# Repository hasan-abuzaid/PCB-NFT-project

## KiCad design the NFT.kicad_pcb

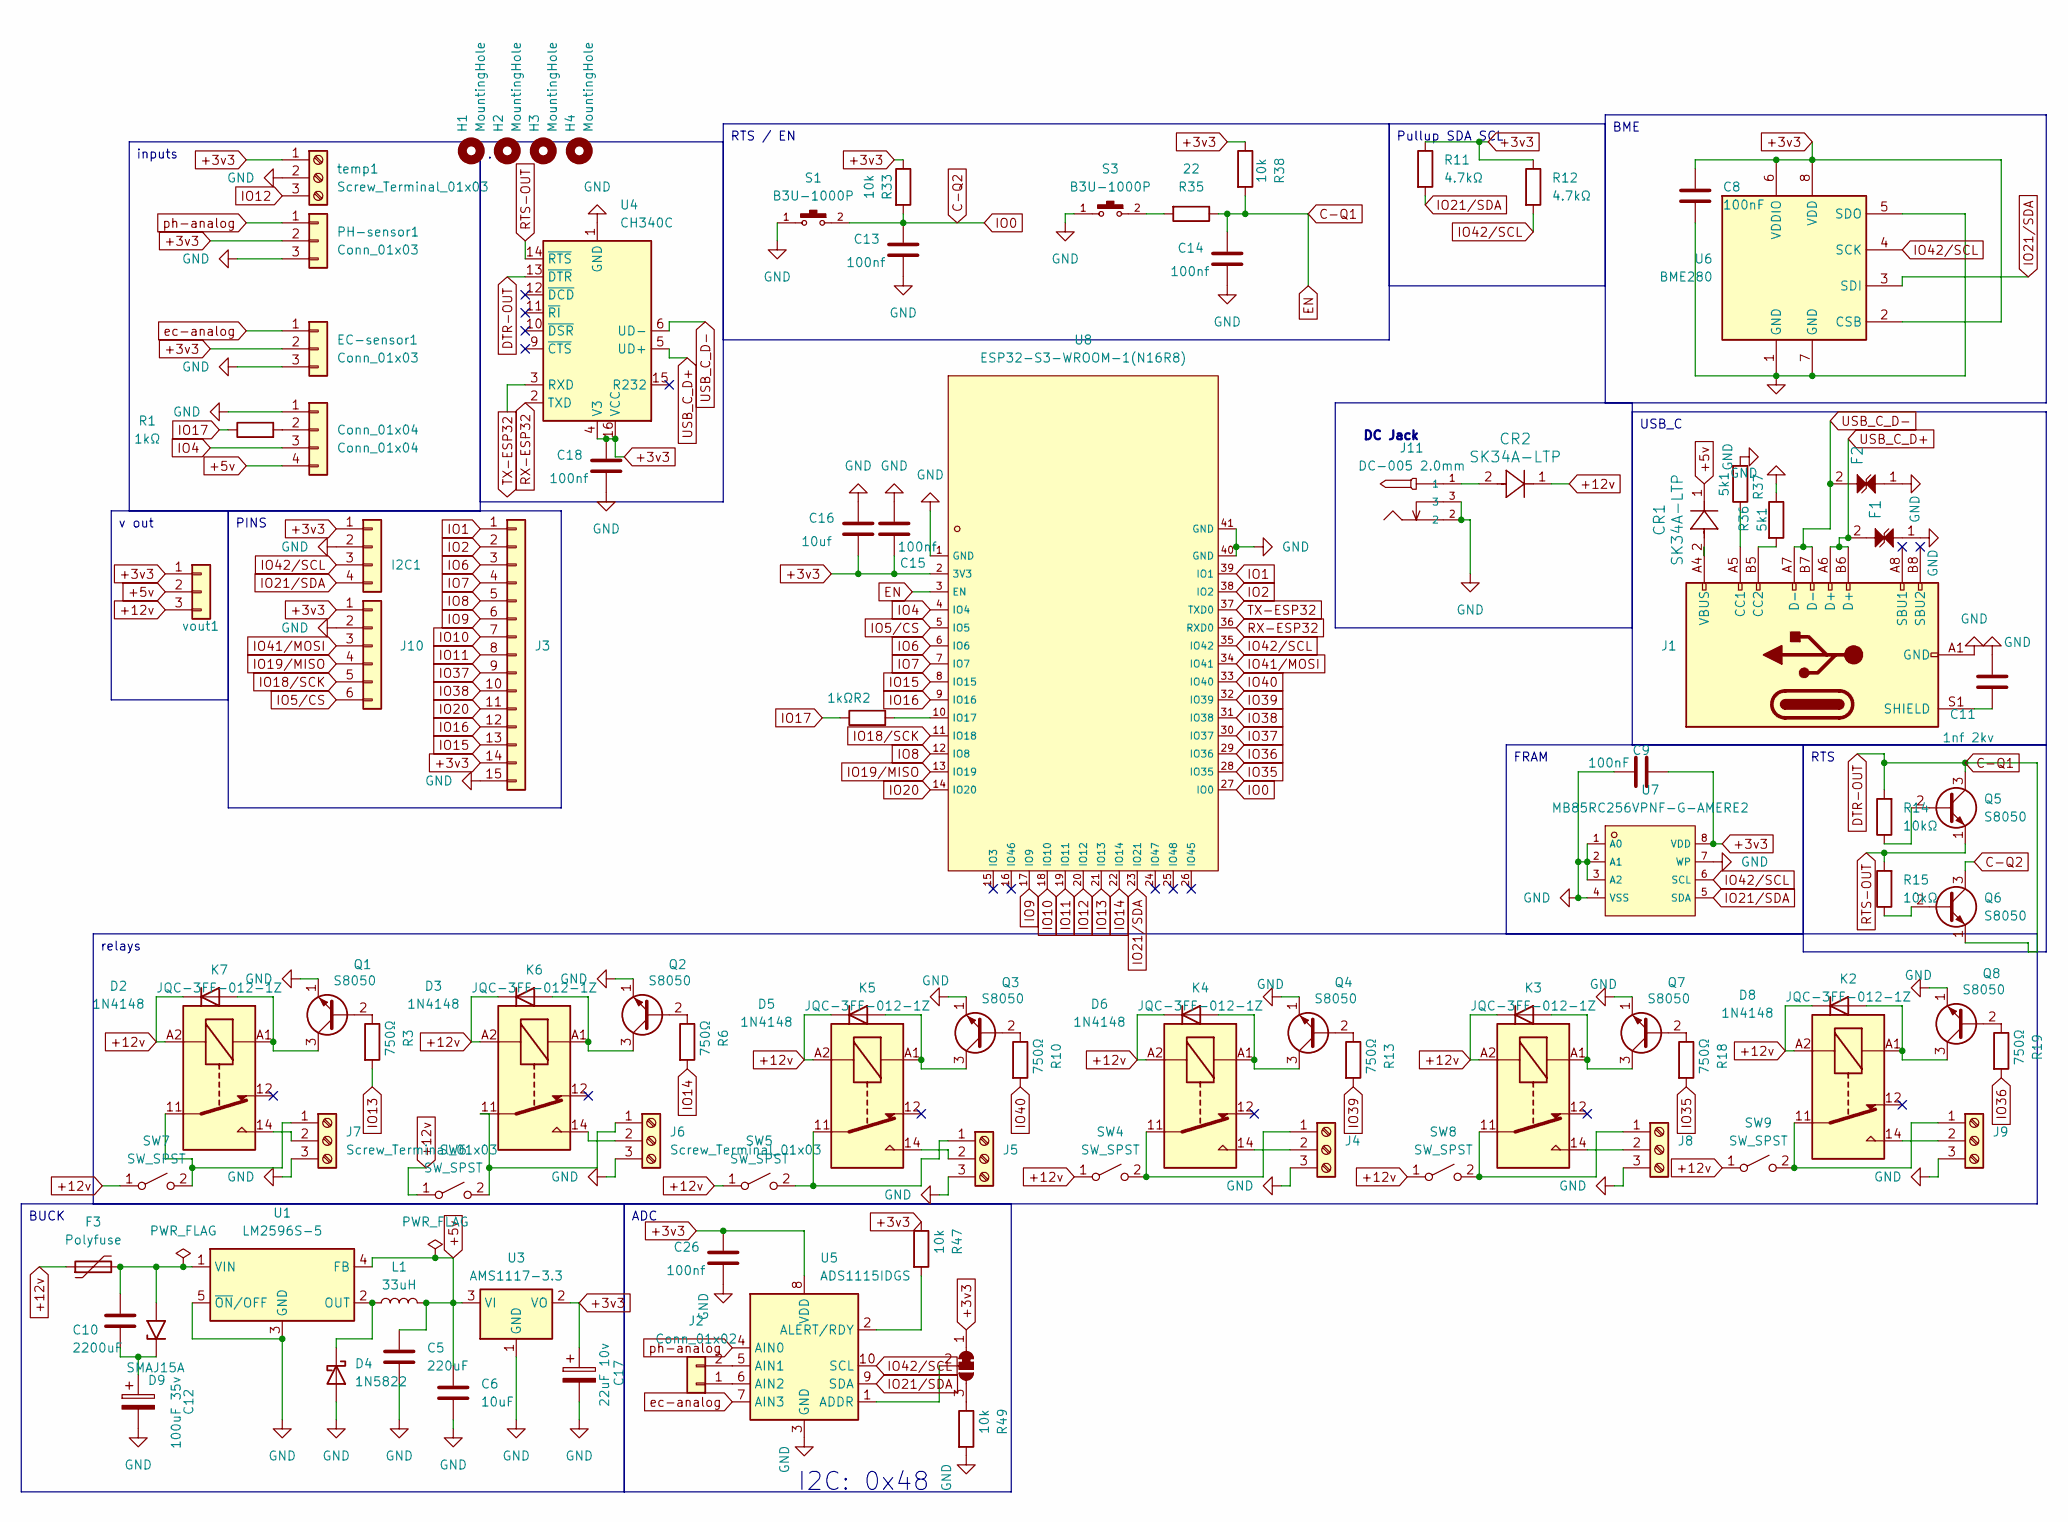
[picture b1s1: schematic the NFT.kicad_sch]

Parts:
C5: 220uF; C_Elec_5x5.4; LCSC part C3345
C6: 10uF; C_0805_2012Metric
C8, C9: 100nF; C_0805_2012Metric
C10: 2200uF; CP_Radial_D12.5mm_P5.00mm
C11: 1nf 2kv; C_1206_3216Metric; LCSC C23631
C12: 100uF 35v; CP_Elec_6.3x7.7
C13, C14, C15, C18, C26: 100nf; C_0805_2012Metric; LCSC C476766
C16: 10uf; C_0805_2012Metric; LCSC C95841
C17: 22uF 10v; CP_Elec_5x5.4; LCSC part C602037
CR1, CR2: SK34A-LTP; SMADO-214AC_MCC; LCSC C85269
Conn_01x04: Conn_01x04; PinSocket_1x04_P2.54mm_Vertical; LCSC part C53055674
D2, D3, D5, D6, D7, D8: 1N4148; D_SOD-123
D4: 1N5822; D_SMC
D9: SMAJ15A; D_SMA
EC-sensor1: Conn_01x03; PinHeader_1x03_P2.54mm_Vertical; LCSC part C49257
F1, F2: PGB1010603MRHF; FUSE_PGB10106_LTF; LCSC C2649884
F3: Polyfuse; Fuse_2920_7451Metric_Pad2.10x5.45mm_HandSolder; LCSC part C70138
H1, H2, H3, H4: MountingHole; MountingHole_3.2mm_M3_ISO7380
I2C1: Conn_01x04; PinHeader_1x04_P2.54mm_Vertical; LCSC part C53055674
J1: USB_C_Receptacle_USB2.0_16P; USB_C_Standing; LCSC part C720628
J2: Conn_01x02; PinHeader_1x02_P2.54mm_Vertical; LCSC part C53055672
J3: Conn_01x15; PinHeader_1x15_P2.54mm_Vertical; LCSC part C2932704
J4, J5, J6, J7, J8, J9: Screw_Terminal_01x03; TerminalBlock_Phoenix_MKDS-1,5-3-5.08_1x03_P5.08mm_Horizont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; LCSC part C395869
J10: Conn_01x06; PinHeader_1x06_P2.54mm_Vertical; LCSC part C32713272
J11: DC-005 2.0mm; C84007_DC-IN-TH_DC-005C-20A; LCSC C84007
JP11: SolderJumper_3_Bridged12; SolderJumper-3_P1.3mm_Bridged12_Pad1.0x1.5mm
K2, K3, K4, K5, K6, K7: JQC-3FF-012-1Z; Relay_SPDT_Hongfa_JQC-3FF_0XX-1Z; LCSC part C2976875
L1: 33uH; L_12x12mm_H6mm
PH-sensor1: Conn_01x03; PinHeader_1x03_P2.54mm_Vertical; LCSC part C49257
Q1, Q2, Q3, Q4, Q5, Q6, Q7, Q8: S8050; SOT-23
R1, R2: 1kΩ; R_0805_2012Metric
R3, R6, R10, R13, R18, R19: 750Ω; R_0805_2012Metric
R11, R12: 4.7kΩ; R_0805_2012Metric
R14, R15: 10kΩ; R_0805_2012Metric
R33, R38, R47, R49: 10k; R_0805_2012Metric; LCSC C17414
R35: 22; R_0805_2012Metric; LCSC C17561
R36, R37: 5k1; R_0805_2012Metric; LCSC C2930296
S1, S3: B3U-1000P; SW_B3U-1000P; LCSC C231329
SW4, SW5, SW6, SW7, SW8, SW9: SW_SPST; C515802_SW-SMD_NSI-10S; LCSC part C515802
U1: LM2596S-5; TO-263-5_TabPin3
U3: AMS1117-3.3; SOT-223-3_TabPin2
U4: CH340C; SOIC-16_3.9x9.9mm_P1.27mm
U5: ADS1115IDGS; TSSOP-10_3x3mm_P0.5mm
U6: BME280; Bosch_LGA-8_2.5x2.5mm_P0.65mm_ClockwisePinNumbering
U7: MB85RC256VPNF-G-AMERE2; C45273903_SOP-8_L4_9-W3_9-P1_27-LS6_0-BL; LCSC C45273903
U8: ESP32-S3-WROOM-1(N16R8); C2913202_WIRELM-SMD_ESP32-S3-WROOM-1; LCSC C2913202
temp1: Screw_Terminal_01x03; C474921_CONN-TH_3P-P2_54_KF128-2_54-3P; LCSC part C395869
vout1: Conn_01x03; PinHeader_1x03_P2.54mm_Vertical; LCSC part C49257

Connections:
+3v3: C8.2, C9.1, C15.2, C16.1, C17.1, C18.2, C26.2, EC-sensor1.2, I2C1.1, J3.14, J10.1, JP11.1 (A), PH-sensor1.2, R11.1, R12.1, R33.1, R38.1, R47.1, U3.2 (VO), U4.4 (V3), U4.16 (VCC), U5.8 (VDD), U6.2 (CSB), U6.6 (VDDIO), U6.8 (VDD), U7.8 (VDD), U8.2 (3V3), temp1.1, vout1.1; also elsewhere on the board
+5v: C5.1, C6.1, CR1.1, Conn_01x04.4, L1.2, U1.4 (FB), U3.3 (VI), vout1.2
+12v: CR2.1, D2.1 (K), D3.1 (K), D5.1 (K), D6.1 (K), D7.1 (K), D8.1 (K), F3.1, K2.A2, K3.A2, K4.A2, K5.A2, K6.A2, K7.A2, SW4.1 (A), SW5.1 (A), SW6.1 (A), SW7.1 (A), SW8.1 (A), SW9.1 (A), vout1.3; also elsewhere on the board
C-Q1: C14.2, Q5.3 (C), Q6.1 (E), R14.2, R35.1, R38.2, U4.13 (~DTR), U8.3 (EN); also elsewhere on the board
C-Q2: C13.2, Q6.3 (C), R33.2, S1.2, U8.27 (IO0); also elsewhere on the board
GND: C5.2, C6.2, C8.1, C9.2, C11.2, C12.2, C13.1, C14.1, C15.1, C16.2, C17.2, C18.1, C26.1, Conn_01x04.1, D4.2 (A), EC-sensor1.3, F1.1, F2.1, I2C1.2, J1.A1 (GND), J1.A12 (GND), J1.B1 (GND), J1.B12 (GND), J3.15, J4.3, J5.3, J6.3, J7.3, J8.3, J9.3, J10.2, J11.2, J11.3, PH-sensor1.3, Q1.1 (E), Q2.1 (E), Q3.1 (E), Q4.1 (E), Q7.1 (E), Q8.1 (E), R36.1, R37.2, R49.2, S1.1, S3.1, U1.3 (GND), U1.5 (~ON/OFF), U3.1 (GND), U4.1 (GND), U5.3 (GND), U6.1 (GND), U6.5 (SDO), U6.7 (GND), U7.1 (A0), U7.2 (A1), U7.3 (A2), U7.4 (VSS), U7.7 (WP), U8.1 (GND), U8.40 (GND), U8.41 (GND), temp1.2; also elsewhere on the board
IO1: J3.1, U8.39 (IO1)
IO2: J3.2, U8.38 (IO2)
IO4: Conn_01x04.3, U8.4 (IO4)
IO5/CS: J10.6, U8.5 (IO5)
IO6: J3.3, U8.6 (IO6)
IO7: J3.4, U8.7 (IO7)
IO8: J3.5, U8.12 (IO8)
IO9: J3.6, U8.17 (IO9)
IO10: J3.7, U8.18 (IO10)
IO11: J3.8, U8.19 (IO11)
IO12: U8.20 (IO12), temp1.3
IO13: R3.2, U8.21 (IO13)
IO14: R6.2, U8.22 (IO14)
IO15: J3.13, U8.8 (IO15)
IO16: J3.12, U8.9 (IO16)
IO17: Conn_01x04.2, R1.1, R1.2, R2.1
IO18/SCK: J10.5, U8.11 (IO18)
IO19/MISO: J10.4, U8.13 (IO19)
IO20: J3.11, U8.14 (IO20)
IO21/SDA: I2C1.4, R11.2, U5.9 (SDA), U6.3 (SDI), U7.5 (SDA), U8.23 (IO21)
IO35: R18.2, U8.28 (IO35)
IO36: R19.2, U8.29 (IO36)
IO37: J3.9, U8.30 (IO37)
IO38: J3.10, U8.31 (IO38)
IO39: R13.2, U8.32 (IO39)
IO40: R10.2, U8.33 (IO40)
IO41/MOSI: J10.3, U8.34 (IO41)
IO42/SCL: I2C1.3, R12.2, U5.10 (SCL), U6.4 (SCK), U7.6 (SCL), U8.35 (IO42); also elsewhere on the board
unnamed: CR1.2, J1.A4 (VBUS), J1.A9 (VBUS), J1.B4 (VBUS), J1.B9 (VBUS)
unnamed: CR2.2, J11.1
unnamed: D2.2 (A), K7.A1, Q1.3 (C)
unnamed: D3.2 (A), K6.A1, Q2.3 (C)
unnamed: D4.1 (K), L1.1, U1.2 (OUT)
unnamed: D5.2 (A), K5.A1, Q3.3 (C)
unnamed: D6.2 (A), K4.A1, Q4.3 (C)
unnamed: D7.2 (A), K3.A1, Q7.3 (C)
unnamed: D8.2 (A), K2.A1, Q8.3 (C)
unnamed: C10.2, C12.1, D9.1 (A1)
unnamed: C10.1, D9.2 (A2), F3.2, U1.1 (VIN)
unnamed: J1.A5 (CC1), R37.1
unnamed: J1.B5 (CC2), R36.2
unnamed: C11.1, J1.S1 (SHIELD)
unnamed: J2.1, U5.6 (AIN2)
unnamed: J2.2, U5.5 (AIN1)
unnamed: J4.1, K4.11, SW4.2 (B)
unnamed: J4.2, K4.14
unnamed: J5.1, K5.11, SW5.2 (B)
unnamed: J5.2, K5.14
unnamed: J6.1, K6.11, SW6.2 (B)
unnamed: J6.2, K6.14
unnamed: J7.1, K7.11, SW7.2 (B)
unnamed: J7.2, K7.14
unnamed: J8.1, K3.11, SW8.2 (B)
unnamed: J8.2, K3.14
unnamed: J9.1, K2.11, SW9.2 (B)
unnamed: J9.2, K2.14
unnamed: JP11.3 (B), R49.1
unnamed: JP11.2 (C), U5.1 (ADDR)
unnamed: Q1.2 (B), R3.1
unnamed: Q2.2 (B), R6.1
unnamed: Q3.2 (B), R10.1
unnamed: Q4.2 (B), R13.1
unnamed: Q5.2 (B), R14.1
unnamed: Q6.2 (B), R15.1
unnamed: Q7.2 (B), R18.1
unnamed: Q8.2 (B), R19.1
unnamed: R35.2, S3.2
unnamed: R47.2, U5.2 (ALERT/RDY)
unnamed 74: R2.2, U8.10 (IO17); also elsewhere on the board
RTS-OUT: Q5.1 (E), R15.2, U4.14 (~RTS)
RX-ESP32: U4.2 (TXD), U8.36 (RXD0)
TX-ESP32: U4.3 (RXD), U8.37 (TXD0)
USB_C_D+: F1.2, J1.A6 (D+), J1.B6 (D+), U4.5 (UD+)
USB_C_D-: F2.2, J1.A7 (D-), J1.B7 (D-), U4.6 (UD-)
ec-analog: EC-sensor1.1, U5.7 (AIN3)
ph-analog: PH-sensor1.1, U5.4 (AIN0)

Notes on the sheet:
I2C: 0x48
FRAM
ADC
relays
PINS
RTS / EN
v out
RTS
Pullup SDA SCL
BUCK
BME
DC Jack
USB_C
inputs

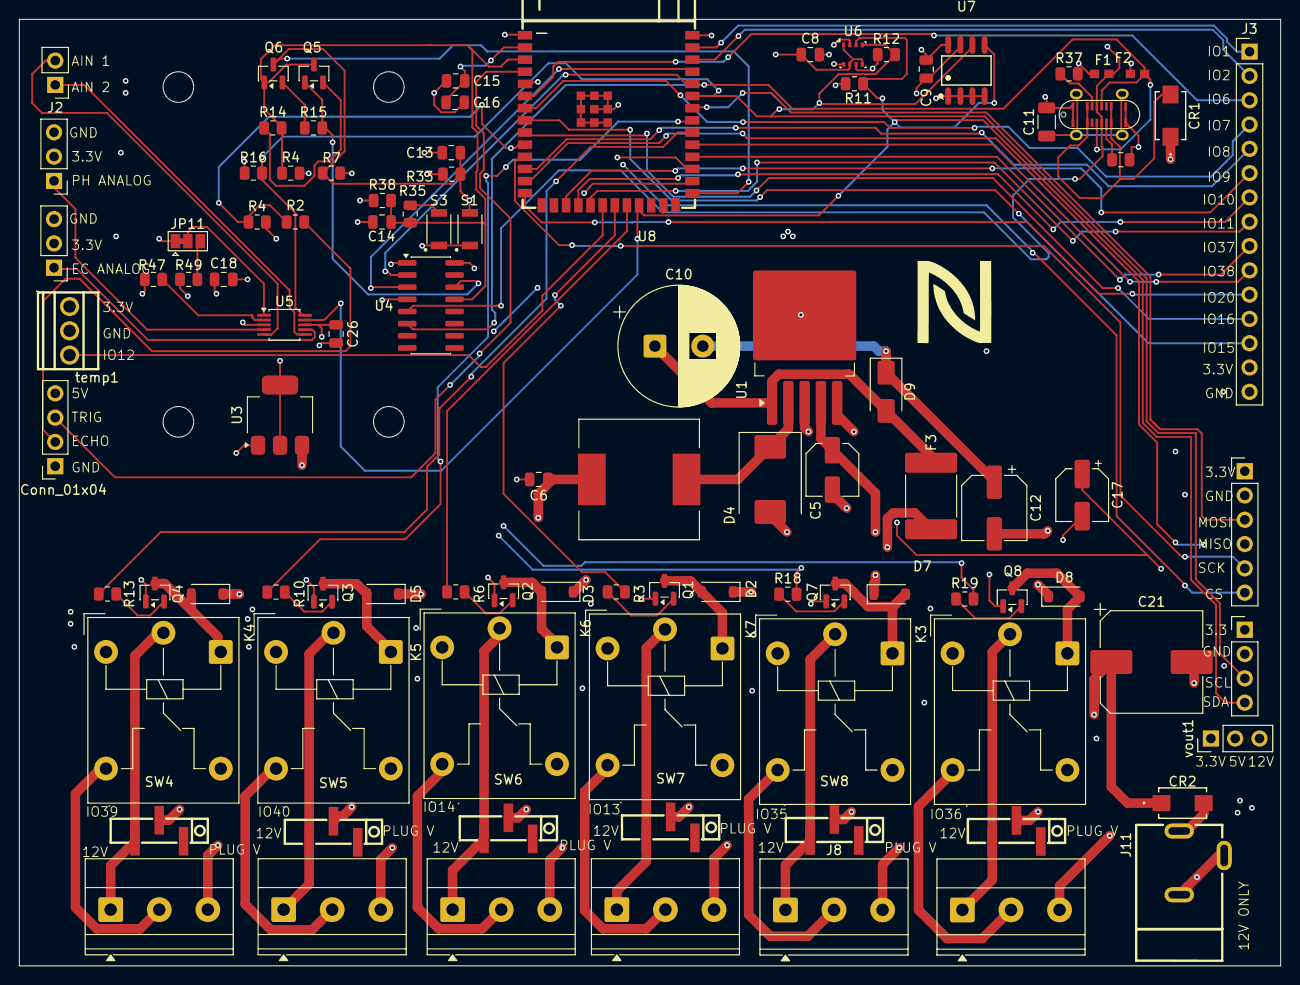
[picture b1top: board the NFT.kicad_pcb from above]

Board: 4 copper layers, 131.9 x 99.0 mm, 102 parts (0 on the bottom side), 82 nets.

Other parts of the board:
C21: 1000uf; CP_Elec_10x10.5
R4, R7: 10kΩ; R_0805_2012Metric
R4#2: 2kΩ; R_0805_2012Metric
R16: 4.7kΩ; R_0805_2012Metric

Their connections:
+3v3: R4.2, R7.2, R16.1; also elsewhere on the board
+12v: C21.1; also elsewhere on the board
C-Q1: R4.1; also elsewhere on the board
C-Q2: R7.1; also elsewhere on the board
GND: C21.2, R4#2.2; also elsewhere on the board
IO42/SCL: R16.2; also elsewhere on the board
unnamed 74: R4#2.1; also elsewhere on the board
